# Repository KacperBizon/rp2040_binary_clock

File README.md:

# rp2040 binary clock

## Flashing
1. Hold BOOTSEL button while plugging the USB
2. mount the device (RPI-RP2)
3. Drag the rp2040_binary_clock.uf2 to RPI-RP2

## Building from Source (Pico C/C++ SDK)
### Prerequisites
- Install CMake and Make
- Install arm-none-eabi-gcc
- Clone the [Raspberry Pi Pico SDK](https://github.com/raspberrypi/pico-sdk), ensure the submodules are initialized and set PICO_SDK_PATH.

### Compilation
```bash
git clone https://github.com/KacperBizon/rp2040_binary_clock.git
cd rp2040_binary_clock/firmware
mkdir build
cd build
cmake ..
make
```

## Optional resistors
- R4 - 10K - use only when having problems with writing to memory
- R25 - 1K - use only with lithium rechargeable batteries

## License & Acknowledgments
This project is distributed under the [MIT License](LICENSE).

Third-Party Components:
The `firmware/pico_sdk_import.cmake` file included in this repository is the intellectual property of Raspberry Pi (Trading) Ltd. and is distributed under the BSD 3-Clause License.

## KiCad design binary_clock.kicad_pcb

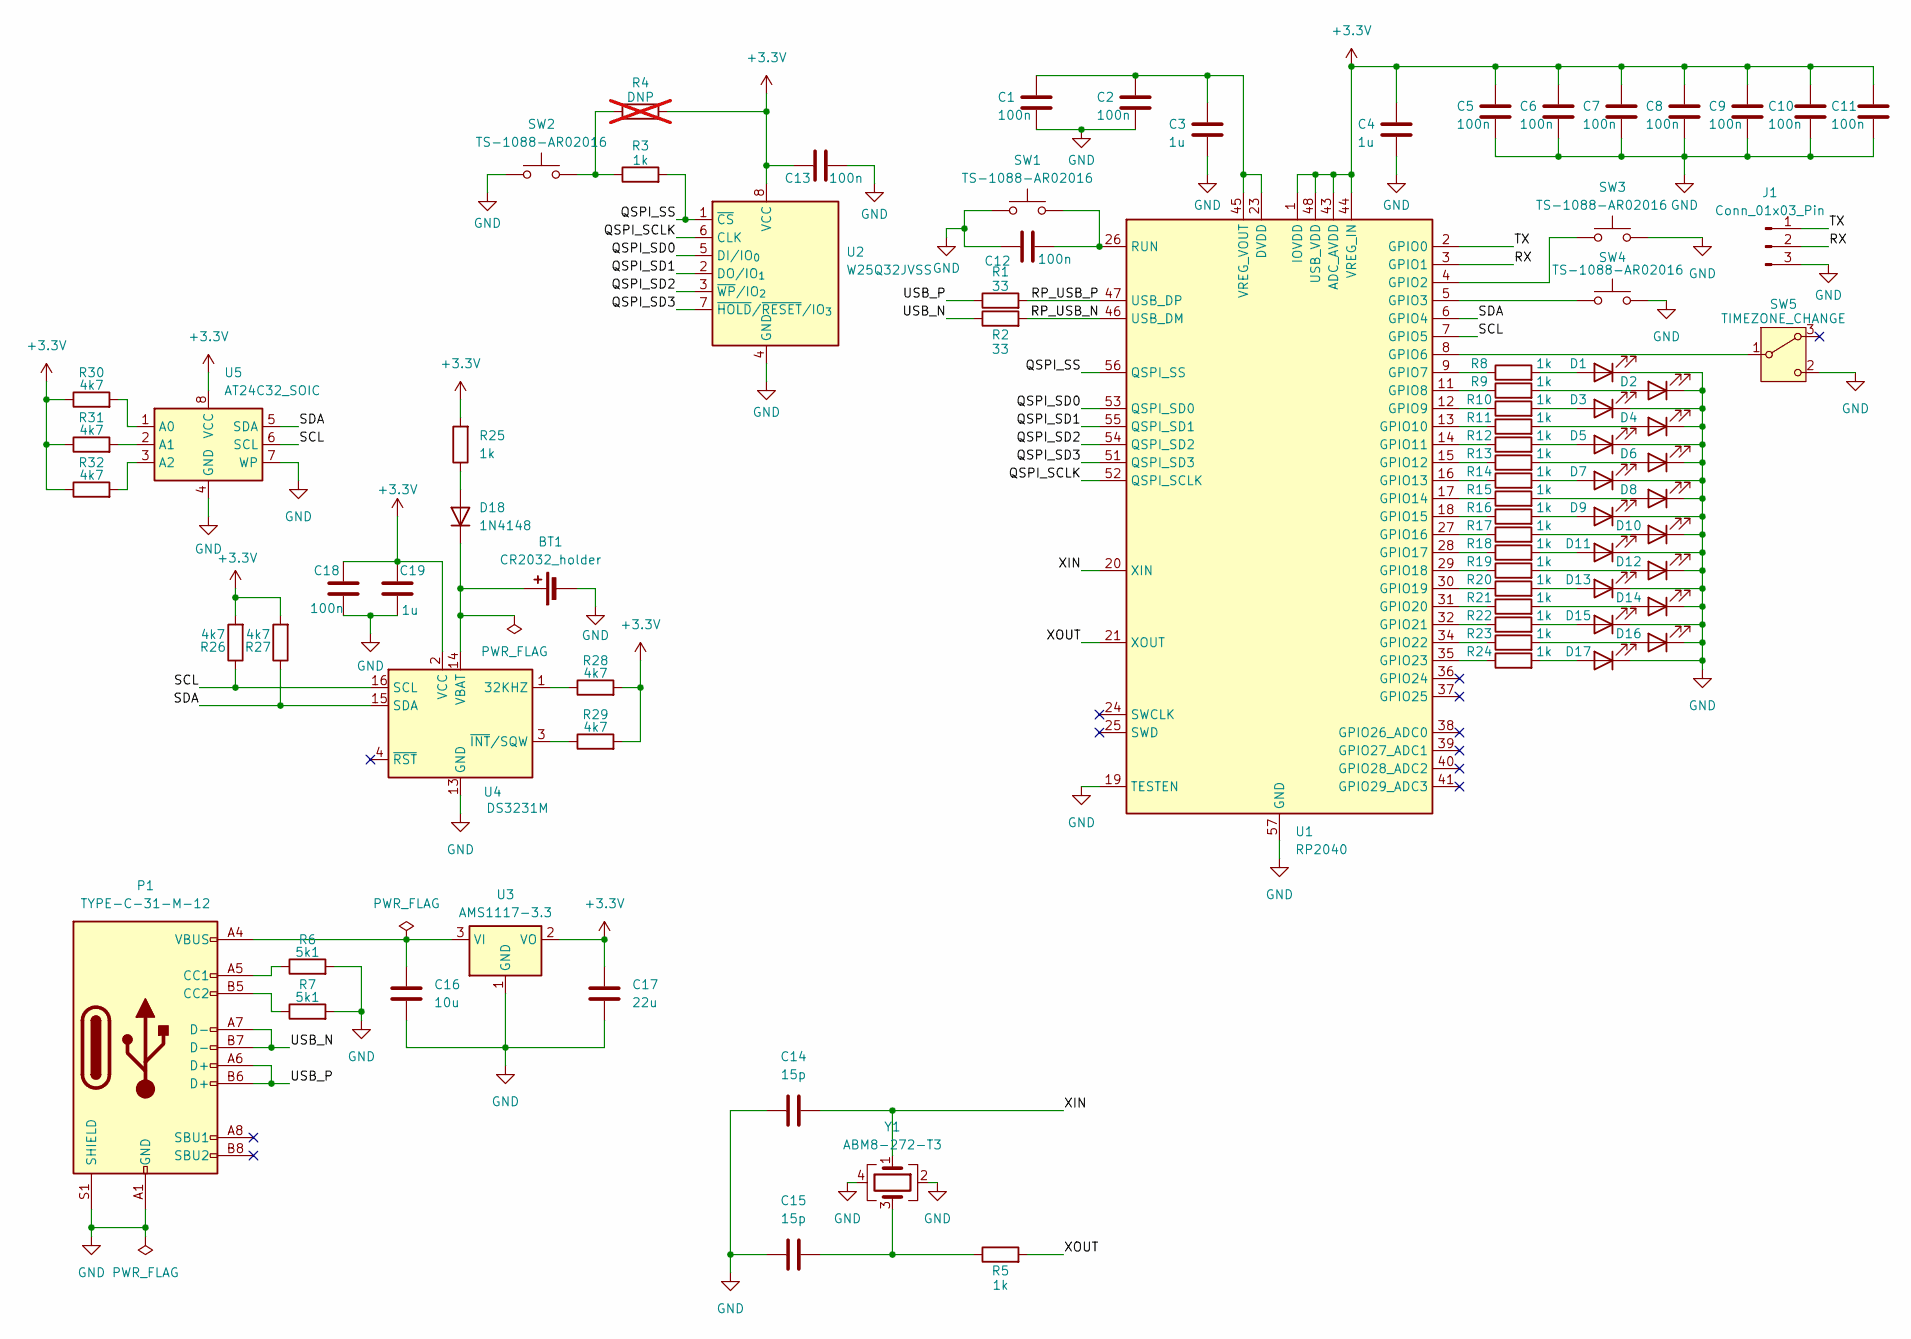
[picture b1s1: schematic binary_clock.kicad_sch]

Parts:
BT1: CR2032_holder; Battery_Holder_Coin_2032_BS-7
C1, C2, C5, C6, C7, C8, C9, C10, C11, C12, C13, C18: 100n; C_0603_1608Metric
C3, C4, C19: 1u; C_0603_1608Metric
C14, C15: 15p; C_0603_1608Metric
C16: 10u; C_0603_1608Metric
C17: 22u; C_0603_1608Metric
D1, D2, D3, D4, D5, D6, D7, D8, D9, D10, D11, D12, D13, D14, D15, D16, D17: LED; LED_D3.0mm
D18: 1N4148; D_DO-35_SOD27_P7.62mm_Horizontal
J1: Conn_01x03_Pin; PinHeader_1x03_P2.54mm_Vertical
P1: TYPE-C-31-M-12; USB_C_Receptacle_HRO_TYPE-C-31-M-12
R1, R2: 33; R_0603_1608Metric
R3, R5, R8, R9, R10, R11, R12, R13, R14, R15, R16, R17, R18, R19, R20, R21, R22, R23, R24: 1k; R_0603_1608Metric
R4: DNP; R_Axial_DIN0207_L6.3mm_D2.5mm_P7.62mm_Horizontal; not fitted
R6, R7: 5k1; R_0603_1608Metric
R25: 1k; R_Axial_DIN0207_L6.3mm_D2.5mm_P7.62mm_Horizontal
R26, R27, R28, R29, R30, R31, R32: 4k7; R_0603_1608Metric
SW1, SW2, SW3, SW4: TS-1088-AR02016; SW_SPST_TS-1088-xR020
SW5: TIMEZONE_CHANGE; SW_Slide_8.6x3.8x7.0_P2.54mm
U1: RP2040; QFN-56-1EP_7x7mm_P0.4mm_EP3.2x3.2mm
U2: W25Q32JVSS; SOIC-8_5.3x5.3mm_P1.27mm
U3: AMS1117-3.3; SOT-223-3_TabPin2
U4: DS3231M; SOIC-16W_7.5x10.3mm_P1.27mm
U5: AT24C32_SOIC; SOIC-8_3.9x4.9mm_P1.27mm
Y1: ABM8-272-T3; Crystal_SMD_Abracon_ABM8G-4Pin_3.2x2.5mm

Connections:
+3.3V: C4.2, C5.2, C6.2, C7.2, C8.2, C9.2, C10.2, C11.2, C13.2, C17.2, C18.2, C19.1, R4.2, R25.2, R26.2, R27.2, R28.2, R29.2, R30.1, R31.1, R32.1, U1.1 (IOVDD), U1.10 (IOVDD), U1.22 (IOVDD), U1.33 (IOVDD), U1.42 (IOVDD), U1.43 (ADC_AVDD), U1.44 (VREG_IN), U1.48 (USB_VDD), U1.49 (IOVDD), U2.8 (VCC), U3.2 (VO), U4.2 (VCC), U5.8 (VCC)
/QSPI_SCLK: U1.52 (QSPI_SCLK), U2.6 (CLK)
/QSPI_SD0: U1.53 (QSPI_SD0), U2.5 (DI/IO_{0})
/QSPI_SD1: U1.55 (QSPI_SD1), U2.2 (DO/IO_{1})
/QSPI_SD2: U1.54 (QSPI_SD2), U2.3 (~WP/IO_{2})
/QSPI_SD3: U1.51 (QSPI_SD3), U2.7 (~HOLD/~RESET/IO_{3})
/QSPI_SS: R3.2, U1.56 (QSPI_SS), U2.1 (~CS)
/RP_USB_N: R2.2, U1.46 (USB_DM)
/RP_USB_P: R1.2, U1.47 (USB_DP)
/RX: J1.2, U1.3 (GPIO1)
/SCL: R26.1, U1.7 (GPIO5), U4.16 (SCL), U5.6 (SCL)
/SDA: R27.1, U1.6 (GPIO4), U4.15 (SDA), U5.5 (SDA)
/TX: J1.1, U1.2 (GPIO0)
/USB_N: P1.A7 (D-), P1.B7 (D-), R2.1
/USB_P: P1.A6 (D+), P1.B6 (D+), R1.1
/XIN: C14.1, U1.20 (XIN), Y1.1
/XOUT: R5.2, U1.21 (XOUT)
GND: BT1.2 (-), C1.1, C2.1, C3.1, C4.1, C5.1, C6.1, C7.1, C8.1, C9.1, C10.1, C11.1, C12.2, C13.1, C14.2, C15.2, C16.1, C17.1, C18.1, C19.2, D1.1 (K), D2.1 (K), D3.1 (K), D4.1 (K), D5.1 (K), D6.1 (K), D7.1 (K), D8.1 (K), D9.1 (K), D10.1 (K), D11.1 (K), D12.1 (K), D13.1 (K), D14.1 (K), D15.1 (K), D16.1 (K), D17.1 (K), J1.3, P1.A1 (GND), P1.A12 (GND), P1.B1 (GND), P1.B12 (GND), P1.S1 (SHIELD), R6.2, R7.2, SW1.1, SW2.1, SW3.2, SW4.2, SW5.2 (C), U1.19 (TESTEN), U1.57 (GND), U2.4 (GND), U3.1 (GND), U4.5 (GND), U4.6 (GND), U4.7 (GND), U4.8 (GND), U4.9 (GND), U4.10 (GND), U4.11 (GND), U4.12 (GND), U4.13 (GND), U5.4 (GND), U5.7 (WP), Y1.2, Y1.4
unnamed: BT1.1 (+), D18.1 (K), U4.14 (VBAT)
unnamed: C15.1, R5.1, Y1.3
unnamed: D1.2 (A), R8.2
unnamed: D2.2 (A), R9.2
unnamed: D3.2 (A), R10.2
unnamed: D4.2 (A), R11.2
unnamed: D5.2 (A), R12.2
unnamed: D6.2 (A), R13.2
unnamed: D7.2 (A), R14.2
unnamed: D8.2 (A), R15.2
unnamed: D9.2 (A), R16.2
unnamed: D10.2 (A), R17.2
unnamed: D11.2 (A), R18.2
unnamed: D12.2 (A), R19.2
unnamed: D13.2 (A), R20.2
unnamed: D14.2 (A), R21.2
unnamed: D15.2 (A), R22.2
unnamed: D16.2 (A), R23.2
unnamed: D17.2 (A), R24.2
unnamed: D18.2 (A), R25.1
unnamed: P1.A5 (CC1), R6.1
unnamed: P1.B5 (CC2), R7.1
unnamed: R3.1, R4.1, SW2.2
unnamed: SW5.1 (B), U1.8 (GPIO6)
unnamed: SW3.1, U1.4 (GPIO2)
unnamed: SW4.1, U1.5 (GPIO3)
unnamed: R8.1, U1.9 (GPIO7)
unnamed: R9.1, U1.11 (GPIO8)
unnamed: R10.1, U1.12 (GPIO9)
unnamed: R11.1, U1.13 (GPIO10)
unnamed: R12.1, U1.14 (GPIO11)
unnamed: R13.1, U1.15 (GPIO12)
unnamed: R14.1, U1.16 (GPIO13)
unnamed: R15.1, U1.17 (GPIO14)
unnamed: R16.1, U1.18 (GPIO15)
unnamed: R17.1, U1.27 (GPIO16)
unnamed: R18.1, U1.28 (GPIO17)
unnamed: R19.1, U1.29 (GPIO18)
unnamed: R20.1, U1.30 (GPIO19)
unnamed: R21.1, U1.31 (GPIO20)
unnamed: R22.1, U1.32 (GPIO21)
unnamed: R23.1, U1.34 (GPIO22)
unnamed: R24.1, U1.35 (GPIO23)
unnamed: C12.1, SW1.2, U1.26 (RUN)
unnamed: C1.2, C2.2, C3.2, U1.23 (DVDD), U1.45 (VREG_VOUT), U1.50 (DVDD)
unnamed: C16.2, P1.A4 (VBUS), P1.A9 (VBUS), P1.B4 (VBUS), P1.B9 (VBUS), U3.3 (VI)
unnamed: R28.1, U4.1 (32KHZ)
unnamed: R29.1, U4.3 (~INT/SQW)
unnamed: R30.2, U5.1 (A0)
unnamed: R31.2, U5.2 (A1)
unnamed: R32.2, U5.3 (A2)

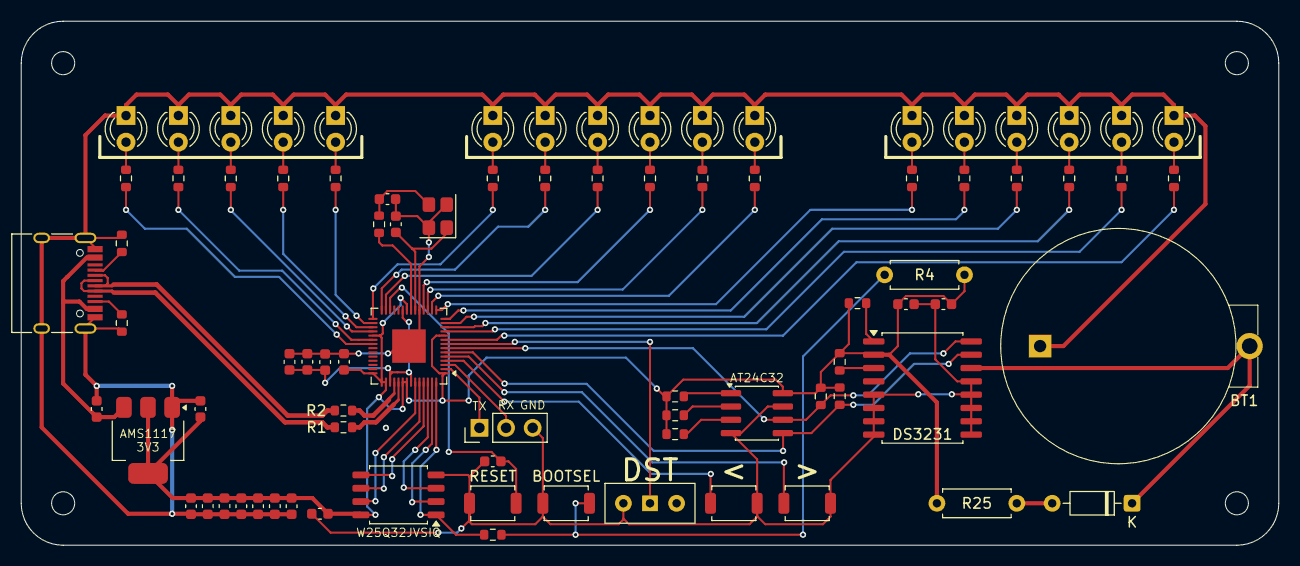
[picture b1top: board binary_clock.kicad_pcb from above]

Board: 2 copper layers, 120.0 x 50.0 mm, 87 parts (0 on the bottom side), 69 nets.

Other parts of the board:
MH1, MH2, MH3, MH4: MountingHole_2.2mm_M2_DIN965

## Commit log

2025-10-31 rp2040 schematic done, wrong usb c
2025-11-01 added switches and labels for i2c0
2025-11-01 added rtc clock and diodes
2025-11-01 half pcb done and cutouts
2025-11-02 pcb finished
2025-11-02 final pcb, ignore production/
2025-11-14 ds1307 example
2025-11-14 cr2032 holder footprint fix, gitignore build
2025-11-14 time optimizaton
2025-11-15 added button function
2025-11-15 Add MIT License
2025-11-15 add readme.md
2025-11-15 photo aspect ratio change
2025-12-20 Widen power tracks and improve solderability
2026-01-08 add Gray code support
2026-02-04 increase clock reliability
2026-02-04 rewrite time changing
2026-02-16 change silkscreen, adjust footprints
2026-03-01 rewrite the project to C
2026-03-01 readme changes
2026-04-02 add USB netclass
2026-04-02 update USB differential pair geometry for 90 ohm coplanar impedance
